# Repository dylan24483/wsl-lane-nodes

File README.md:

# wsl-lane-nodes

Phase 8 of the Westside Lanes Conqueror replacement project. Each Pi 4 controls one lane pair, replacing the QubicaAMF stack (BCU II + QBK-SIx + T-VISION + VDB-99) with direct GPIO control of the AMF 8270 cabinet I/O. Pi nodes connect to WSL-SRV via WebSocket and feed events into the existing wsl_scoring_engine.

## Status: bench rig fully validated (2026-05-06)

**What runs end-to-end on the bench:**

- [x] Pi GPIO + WebSocket + scoring engine + browser display (night-1 prototype, 2026-05-01)
- [x] AEDIKO 8-channel relay HAT + AL-ZARD DST-1R8P-P opto-input bench rig validated
- [x] Per-pair (lanes 21 + 22): 4 inputs (foul × 2 + 2nd-ball × 2) + 4 outputs (cycle × 2 + power × 2)
- [x] Both control modes proven: pulsed cycle + latched power on/off
- [x] Production safety: SIGTERM handler + `try/finally` on `pulse()` + systemd `ExecStopPost=` cleanup (3 of 4 K-mitigations; hardware watchdog is the 4th)
- [x] Foul-event vs ball-detect semantic separation (BALL_EVENT carries pin_mask + foul flag)
- [x] OpenCV pin-detect pipeline skeleton (synthetic-image self-test passes)
- [x] SQLite state persistence — server restarts don't wipe in-progress games
- [x] WebSocket protocol versioning
- [x] Server portable to WSL-SRV (Windows) or stays on Pi for dev

**Active gates before Phase 8a cutover:**

- [ ] Lane 22 characterization visit — see [docs/lane_visit_checklist.md](docs/lane_visit_checklist.md)
- [ ] T-Camera + USB capture dongle on bench — calibrate `pin_detect.PIN_SPOTS` against real frames
- [ ] Hardware watchdog perfboard build — see [docs/hardware_watchdog_design.md](docs/hardware_watchdog_design.md)

## Layout

| Path | What |
|---|---|
| `lane_node/lane_node.py` | Pi-side daemon — multi-lane GPIO, WebSocket client, signal handlers |
| `lane_node/relay_cleanup.py` | Standalone GPIO cleanup script run by systemd `ExecStopPost=` |
| `lane_node/pin_detect.py` | OpenCV pipeline skeleton + synthetic-image self-test |
| `server/lane_node_server.py` | Server — WebSocket + HTTP display + desk simulator UI + `/api/health` |
| `server/state_store.py` | SQLite persistence helpers + CLI for state inspection |
| `systemd/lane-node.service` | systemd unit for production deployment |
| `prototypes/` | Scaffolding scripts that proved individual pieces during night-1 |
| `wsl_scoring_engine.py` | Copied from wsl-systems — handles bowling logic |
| `docs/lane_visit_checklist.md` | On-site procedure for the lane characterization visit |
| `docs/hardware_watchdog_design.md` | CD4538B + MOSFET watchdog circuit spec for the 4th K-pillar |
| `docs/deploy_server_to_wsl_srv.md` | Step-by-step for moving the server to WSL-SRV |

## Run on the Pi

Two SSH sessions, server in one + lane node in the other:

```bash
# Session 1 — server
cd ~/wsl-lane-nodes && source .venv/bin/activate
WSL_MACHINE_LANES=21,22 \
WSL_SCORING_NODE_TOPOLOGY=pi-lane21-22=21,22 \
WSL_ALLOW_UNAUTHENTICATED_BENCH=1 \
python3 server/lane_node_server.py

# Session 2 — lane node daemon
cd ~/wsl-lane-nodes && source .venv/bin/activate
WSL_LANE_NODE_ID=pi-lane21-22 WSL_DIAG_SOURCE_ID=pi-lane21-22 \
WSL_LANES=21,22 WSL_ALLOW_UNAUTHENTICATED_BENCH=1 \
python3 lane_node/lane_node.py
```

Browser at `http://lane-node-dev.local:8766/` — Open Lane / Close Lane / Reset Pins / Power On/Off / Trigger Ball buttons per lane.

## Run server on WSL-SRV instead of Pi

```bash
# On WSL-SRV (Windows): see docs/deploy_server_to_wsl_srv.md
# On the Pi:
WSL_LANE_SERVER_URL=ws://192.168.4.103:8765 \
WSL_LANE_NODE_ID=pi-lane21-22 WSL_DIAG_SOURCE_ID=pi-lane21-22 \
WSL_LANES=21,22 LANE_NODE_TOKEN=<shared-secret> \
WSL_SCORING_NODE_TOKEN=<unique-pi-secret> python3 lane_node/lane_node.py
# (192.168.4.103 = WSL-SRV since the 2026-06-03 eero re-IP; confirm the live IP —
#  the DHCP reservation is still TODO. The old 192.168.86.36 is dead.)
```

## Health check

```bash
curl http://lane-node-dev.local:8766/api/health
```

Returns server uptime, connected node summary, per-lane state, pending foul flags, state DB path.

## State inspection

```bash
python3 server/state_store.py            # print current saved state
python3 server/state_store.py clear      # wipe saved state
```

## Test pin detection on synthetic frames

```bash
python3 lane_node/pin_detect.py
```

Runs 7 synthetic-image test cases (strike, gutter, head pin only down, 7-10 split, etc.) and reports pass/fail. Validates the pipeline shape; real-camera calibration of `PIN_SPOTS` is a separate step.

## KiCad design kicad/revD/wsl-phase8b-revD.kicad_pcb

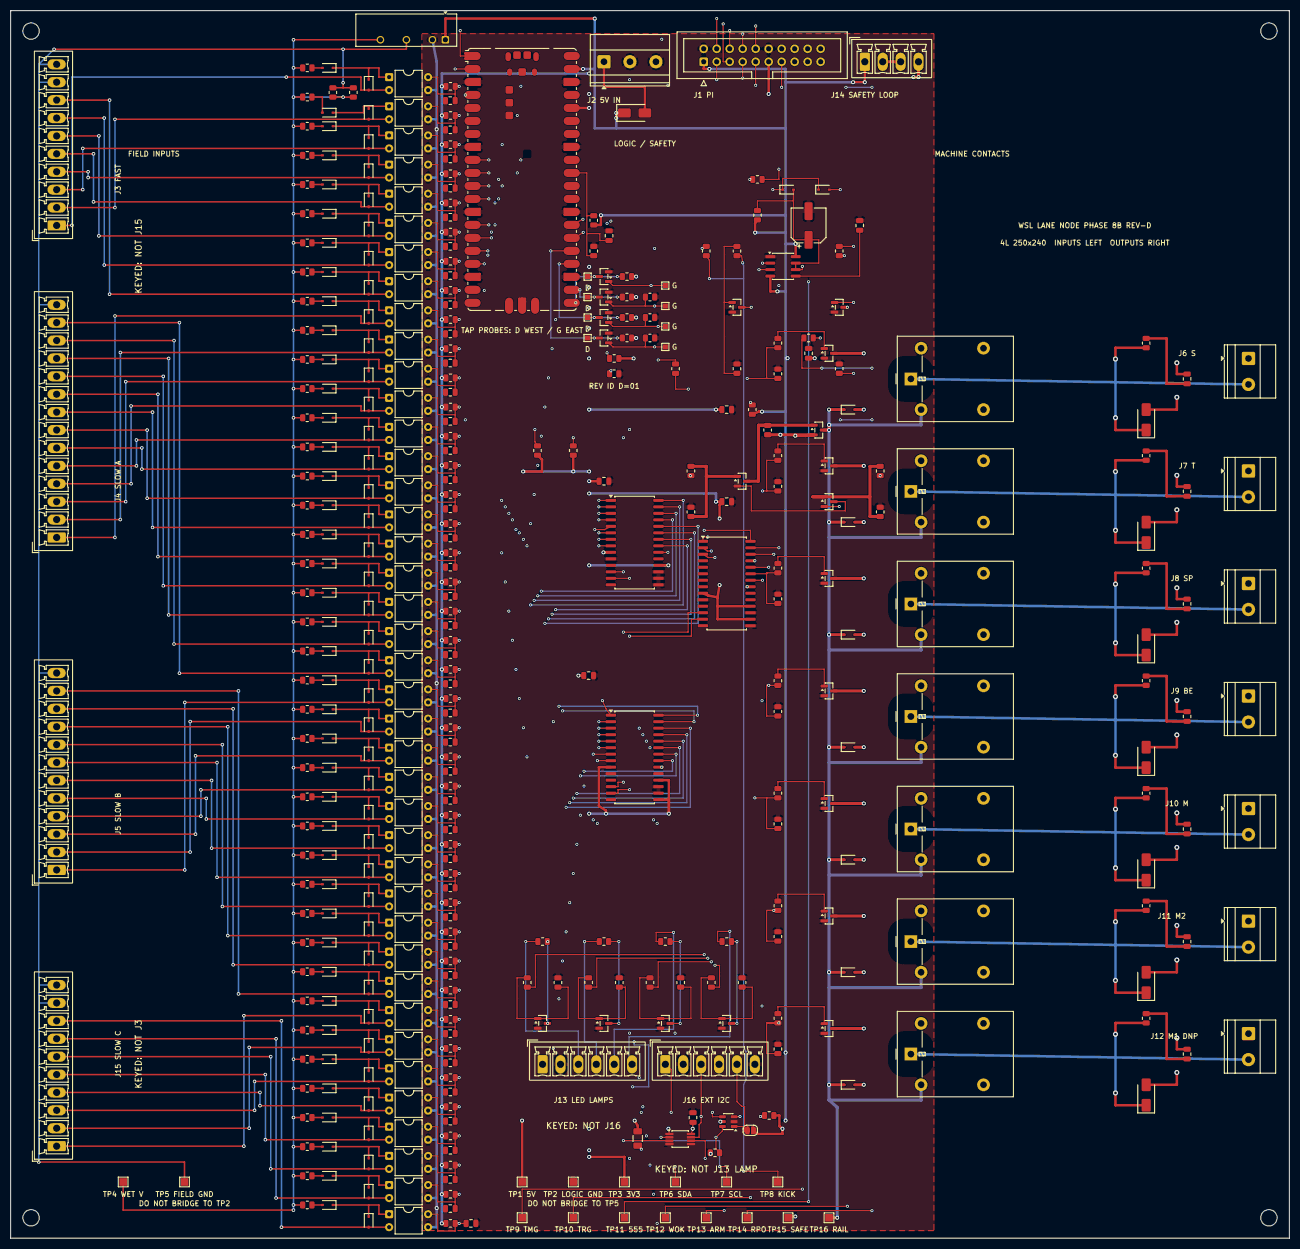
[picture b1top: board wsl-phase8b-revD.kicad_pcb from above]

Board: 4 copper layers, 250.0 x 240.0 mm, 419 parts (0 on the bottom side), 263 nets.

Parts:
A1: RP2040 Pico; RaspberryPi_Pico_SMD
C1, C2, C3, C12, C16: 0.1uF; C_0805_2012Metric
C4, C5, C6, C7, C8, C9, C10: 10nF X2 DNP; C_0805_2012Metric
C11: 100uF/16V; CP_Elec_6.3x5.4
C13: 10nF; C_0805_2012Metric
C14: 10uF; C_0805_2012Metric
C15: 100nF; C_0805_2012Metric
C17, C18, C19, C20, C21, C22, C23, C24: 10nF X7R DNP; C_0805_2012Metric
C25, C26, C27, C28, C29, C30, C31, C32, C33, C34, C35, C36, C37, C38, C39, C40, C41, C42, C43, C44, C45, C46, C47, C48, C49, C50, C51, C52, C53, C54, C55, C56: 2.2uF X7R DNP; C_0805_2012Metric
D1, D3, D5, D7, D9, D11, D13, D15, D16, D18, D19, D20, D21, D22, D23, D24, D25, D26, D27, D28, D29, D30, D31, D32, D33, D34, D35, D36, D37, D38, D39, D40, D41, D42, D43, D44, D45, D46, D47, D48, D49, D50, D51, D52, D53, D54, D55, D56, D57, D58, D59, D60, D61, D62, D63, D64, D65, D66, D67, D68, D69, D70, D71, D72, D73, D74, D75, D76, D77, D78, D79, D80, D81, D82, D83, D84, D85, D86, D87, D88, D89, D90, D91, D92, D93, D94, D95, D96, D97: 1N4148; D_SOD-323
D2, D4, D6, D8, D10, D12, D14: MOV DNP; D_SMA
D17: SS34; D_SMA
F1: 1206L020YR 200mA; Fuse_1206_3216Metric
J1: J_PI; IDC-Header_2x10_P2.54mm_Vertical
J2: J_PWR 5V; TerminalBlock_Phoenix_MKDS-1,5-3-5.08_1x03_P5.08mm_Horizont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
J3: J_FAST_IN; PhoenixContact_MCV_1,5_10-G-3.5_1x10_P3.50mm_Vertical_D1.4
J4: J_SLOW_IN_A; PhoenixContact_MCV_1,5_14-G-3.5_1x14_P3.50mm_Vertical_D1.4
J5: J_SLOW_IN_B; PhoenixContact_MCV_1,5_12-G-3.5_1x12_P3.50mm_Vertical_D1.4
J6: J_MOTION_S 5.08mm; TerminalBlock_Phoenix_MKDS-1,5-2-5.08_1x02_P5.08mm_Horizont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
J7: J_MOTION_T 5.08mm; TerminalBlock_Phoenix_MKDS-1,5-2-5.08_1x02_P5.08mm_Horizont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
J8: J_MOTION_SP 5.08mm; TerminalBlock_Phoenix_MKDS-1,5-2-5.08_1x02_P5.08mm_Horizont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
J9: J_MOTION_BE 5.08mm; TerminalBlock_Phoenix_MKDS-1,5-2-5.08_1x02_P5.08mm_Horizont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
J10: J_MOTION_M 5.08mm; TerminalBlock_Phoenix_MKDS-1,5-2-5.08_1x02_P5.08mm_Horizont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
J11: J_MOTION_M2 5.08mm; TerminalBlock_Phoenix_MKDS-1,5-2-5.08_1x02_P5.08mm_Horizont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
J12: J_MOTION_M1 5.08mm; TerminalBlock_Phoenix_MKDS-1,5-2-5.08_1x02_P5.08mm_Horizont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
J13: J_LAMP_LED; PhoenixContact_MCV_1,5_6-G-3.5_1x06_P3.50mm_Vertical_D1.4
J14: J_SAFETY; PhoenixContact_MCV_1,5_4-G-3.5_1x04_P3.50mm_Vertical_D1.4
J15: J_SLOW_IN_C; PhoenixContact_MCV_1,5_10-G-3.5_1x10_P3.50mm_Vertical_D1.4
J16: J_EXT_I2C; PhoenixContact_MCV_1,5_6-G-3.5_1x06_P3.50mm_Vertical_D1.4
JP1: 3V3 LINK OPEN DNP; SolderJumper-2_P1.3mm_Open_RoundedPad1.0x1.5mm
K1: G5LE S; Relay_SPDT_Omron-G5LE-1
K2: G5LE T; Relay_SPDT_Omron-G5LE-1
K3: G5LE SP; Relay_SPDT_Omron-G5LE-1
K4: G5LE BE; Relay_SPDT_Omron-G5LE-1
K5: G5LE M; Relay_SPDT_Omron-G5LE-1
K6: G5LE M2; Relay_SPDT_Omron-G5LE-1
K7: G5LE M1 DNP; Relay_SPDT_Omron-G5LE-1
MK1, MK2, MK3, MK4: M3; MountingHole_3.2mm_M3
Q1: MMBT3904 S; SOT-23
Q2: MMBT3904 T; SOT-23
Q3: MMBT3904 SP; SOT-23
Q4: MMBT3904 BE; SOT-23
Q5: MMBT3904 M; SOT-23
Q6: MMBT3904 M2; SOT-23
Q7: MMBT3904 M1; SOT-23
Q8: 2N7002 LED L_FIRST; SOT-23
Q9: 2N7002 LED L_SECOND; SOT-23
Q10: 2N7002 LED L_STRIKE; SOT-23
Q11: 2N7002 LED L_FOUL; SOT-23
Q12: AO3400A kick; SOT-23
Q13: AO3400A wdog; SOT-23
Q14: AO3401A rail pass; SOT-23
Q15: MMBT3904 AND ARM; SOT-23
Q16: MMBT3904 AND RP_OK; SOT-23
Q17: 2N7002LT1G TAP 555; SOT-23
Q18: 2N7002LT1G TAP KICK; SOT-23
Q19: 2N7002LT1G TAP ARM; SOT-23
Q20: 2N7002LT1G TAP RPOK; SOT-23
R1, R2, R142, R143: 4.7k; R_0805_2012Metric
R3, R5, R7, R9, R11, R13, R15, R17, R19, R21, R23, R25, R27, R29, R31, R33, R35, R37, R39, R41, R43, R45, R47, R49, R51, R53, R55, R57, R59, R61, R63, R65, R67, R69, R71, R73, R75, R77, R79, R81, R122, R123: 2k2; R_0805_2012Metric
R4, R6, R8, R10, R12, R14, R16, R18, R20, R22, R24, R26, R28, R30, R32, R34, R36, R38, R40, R42, R44, R46, R48, R50, R52, R54, R56, R58, R60, R62, R64, R66, R68, R70, R72, R74, R76, R78, R80, R82: 47k; R_0805_2012Metric
R83, R86, R89, R92, R95, R98, R101, R104, R107, R110, R113, R118, R120: 1k; R_0805_2012Metric
R84, R87, R90, R93, R96, R99, R102, R105, R108, R111, R114, R116, R124, R126, R128: 100k; R_0805_2012Metric
R85, R88, R91, R94, R97, R100, R103: 100R DNP; R_0805_2012Metric
R106, R109, R112, R115: 330R; R_0805_2012Metric
R117, R119, R121, R125, R127, R129, R130, R132, R134, R137, R140, R144, R145: 10k; R_0805_2012Metric
R131, R133, R136, R139: 1M; R_0805_2012Metric
R135, R138, R141: 10M; R_0805_2012Metric
TP1: VCC_5V; TestPoint_Pad_1.5x1.5mm
TP2: GND; TestPoint_Pad_1.5x1.5mm
TP3: VCC_3V3; TestPoint_Pad_1.5x1.5mm
TP4: FIELD_WET_V; TestPoint_Pad_1.5x1.5mm
TP5: FIELD_GND; TestPoint_Pad_1.5x1.5mm
TP6: I2C_SDA; TestPoint_Pad_1.5x1.5mm
TP7: I2C_SCL; TestPoint_Pad_1.5x1.5mm
TP8: WDOG_KICK; TestPoint_Pad_1.5x1.5mm
TP9: WDOG_TIMING_NODE; TestPoint_Pad_1.5x1.5mm
TP10: NE555_TRIG; TestPoint_Pad_1.5x1.5mm
TP11: NE555_OUT; TestPoint_Pad_1.5x1.5mm
TP12: WDOG_OK_PULLDOWN; TestPoint_Pad_1.5x1.5mm
TP13: ARM_PERMIT; TestPoint_Pad_1.5x1.5mm
TP14: RP2040_OK; TestPoint_Pad_1.5x1.5mm
TP15: SAFE_STOP_RETURN; TestPoint_Pad_1.5x1.5mm
TP16: RELAY_ENABLE_RAIL; TestPoint_Pad_1.5x1.5mm
TP17: TAP_GATE_555; TestPoint_Pad_1.0x1.0mm
TP18: TAP_NE555_OUT; TestPoint_Pad_1.0x1.0mm
TP19: TAP_GATE_KICK; TestPoint_Pad_1.0x1.0mm
TP20: TAP_WDOG_KICK; TestPoint_Pad_1.0x1.0mm
TP21: TAP_GATE_ARM; TestPoint_Pad_1.0x1.0mm
TP22: TAP_ARM_PERMIT; TestPoint_Pad_1.0x1.0mm
TP23: TAP_GATE_RPOK; TestPoint_Pad_1.0x1.0mm
TP24: TAP_RP2040_OK; TestPoint_Pad_1.0x1.0mm
U1: MCP23017 MCP_IN_A; SOIC-28W_7.5x17.9mm_P1.27mm
U2: MCP23017 MCP_IN_B; SOIC-28W_7.5x17.9mm_P1.27mm
U3: MCP23017 MCP_OUT_A; SOIC-28W_7.5x17.9mm_P1.27mm
U4: PC817 SA; DIP-4_W7.62mm
U5: PC817 SB; DIP-4_W7.62mm
U6: PC817 SC; DIP-4_W7.62mm
U7: PC817 TA1; DIP-4_W7.62mm
U8: PC817 TA2; DIP-4_W7.62mm
U9: PC817 TB; DIP-4_W7.62mm
U10: PC817 DIELL_L; DIP-4_W7.62mm
U11: PC817 DIELL_R; DIP-4_W7.62mm
U12: PC817 GS1; DIP-4_W7.62mm
U13: PC817 GS2; DIP-4_W7.62mm
U14: PC817 GS3; DIP-4_W7.62mm
U15: PC817 GS4; DIP-4_W7.62mm
U16: PC817 GS5; DIP-4_W7.62mm
U17: PC817 GS6; DIP-4_W7.62mm
U18: PC817 GS7; DIP-4_W7.62mm
U19: PC817 GS8; DIP-4_W7.62mm
U20: PC817 GS9; DIP-4_W7.62mm
U21: PC817 GS10; DIP-4_W7.62mm
U22: PC817 GP; DIP-4_W7.62mm
U23: PC817 OS; DIP-4_W7.62mm
U24: PC817 BS; DIP-4_W7.62mm
U25: PC817 PBZ; DIP-4_W7.62mm
U26: PC817 PBC; DIP-4_W7.62mm
U27: PC817 FOUL; DIP-4_W7.62mm
U28: PC817 TENTH; DIP-4_W7.62mm
U29: PC817 MAN_T; DIP-4_W7.62mm
U30: PC817 MAN_S; DIP-4_W7.62mm
U31: PC817 MAN_SWS; DIP-4_W7.62mm
U32: PC817 MAN_SWSR; DIP-4_W7.62mm
U33: PC817 AUX1; DIP-4_W7.62mm
U34: PC817 AUX2; DIP-4_W7.62mm
U35: PC817 AUX3; DIP-4_W7.62mm
U36: PC817 AUX4; DIP-4_W7.62mm
U37: PC817 AUX5; DIP-4_W7.62mm
U38: PC817 AUX6; DIP-4_W7.62mm
U39: PC817 AUX7; DIP-4_W7.62mm
U40: PC817 AUX8; DIP-4_W7.62mm
U41: PC817 AUX9; DIP-4_W7.62mm
U42: PC817 AUX10; DIP-4_W7.62mm
U43: PC817 AUX11; DIP-4_W7.62mm
U44: NE555; SOIC-8_3.9x4.9mm_P1.27mm
U45: TMA-0505S; Converter_DCDC_TRACO_TMA-05xxS_12xxS_Single_THT
U46: TCA4307DGKR; VSSOP-8_3x3mm_P0.65mm
U47: SRV05-4; SOT-23-6

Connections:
ADC_VCC5_SENSE: A1.31, C15.1, R129.2, R130.1
AND_MID_ARM_RP: Q15.2, Q16.3
ARM_PERMIT: J1.8, R125.1, R136.1, TP13.1
BASE_AND_ARM: Q15.1, R125.2, R126.1
BASE_AND_RP_OK: Q16.1, R127.2, R128.1
BASE_BE: Q4.1, R92.2
BASE_M: Q5.1, R95.2
BASE_M1: Q7.1, R101.2
BASE_M2: Q6.1, R98.2
BASE_S: Q1.1, R83.2
BASE_SP: Q3.1, R89.2
BASE_T: Q2.1, R86.2
COIL_LO_BE: D7.2, K4.5, Q4.3
COIL_LO_M: D9.2, K5.5, Q5.3
COIL_LO_M1: D13.2, K7.5, Q7.3
COIL_LO_M2: D11.2, K6.5, Q6.3
COIL_LO_S: D1.2, K1.5, Q1.3
COIL_LO_SP: D5.2, K3.5, Q3.3
COIL_LO_T: D3.2, K2.5, Q2.3
DRV_BE: R92.1, R93.1, U3.24
DRV_L_FIRST: R104.1, U3.28
DRV_L_FOUL: R113.1, U3.3
DRV_L_SECOND: R107.1, U3.1
DRV_L_STRIKE: R110.1, U3.2
DRV_M: R95.1, R96.1, U3.25
DRV_M1: R101.1, R102.1, U3.27
DRV_M2: R98.1, R99.1, U3.26
DRV_S: R83.1, R84.1, U3.21
DRV_SP: R89.1, R90.1, U3.23
DRV_T: R86.1, R87.1, U3.22
FAST_DIELL_L: A1.16, C23.1, R16.2, U10.4
FAST_DIELL_R: A1.17, C24.1, R18.2, U11.4
FAST_SA: A1.9, C17.1, R4.2, U4.4
FAST_SB: A1.10, C18.1, R6.2, U5.4
FAST_SC: A1.11, C19.1, R8.2, U6.4
FAST_TA1: A1.12, C20.1, R10.2, U7.4
FAST_TA2: A1.14, C21.1, R12.2, U8.4
FAST_TB: A1.15, C22.1, R14.2, U9.4
FIELD_FAST_DIELL_L: D31.2, J3.7, U10.2
FIELD_FAST_DIELL_R: D33.2, J3.8, U11.2
FIELD_FAST_SA: D19.2, J3.1, U4.2
FIELD_FAST_SB: D21.2, J3.2, U5.2
FIELD_FAST_SC: D23.2, J3.3, U6.2
FIELD_FAST_TA1: D25.2, J3.4, U7.2
FIELD_FAST_TA2: D27.2, J3.5, U8.2
FIELD_FAST_TB: D29.2, J3.6, U9.2
FIELD_GND: J3.9, J3.10, J4.14, J5.12, J15.9, J15.10, R122.2, R123.2, TP5.1, U45.4
FIELD_LED_AUX1: D76.1, D77.1, U33.1
FIELD_LED_AUX2: D78.1, D79.1, U34.1
FIELD_LED_AUX3: D80.1, D81.1, U35.1
FIELD_LED_AUX4: D82.1, D83.1, U36.1
FIELD_LED_AUX5: D84.1, D85.1, U37.1
FIELD_LED_AUX6: D86.1, D87.1, U38.1
FIELD_LED_AUX7: D88.1, D89.1, U39.1
FIELD_LED_AUX8: D90.1, D91.1, U40.1
FIELD_LED_AUX9: D92.1, D93.1, U41.1
FIELD_LED_AUX10: D94.1, D95.1, U42.1
FIELD_LED_AUX11: D96.1, D97.1, U43.1
FIELD_LED_BS: D58.1, D59.1, U24.1
FIELD_LED_DIELL_L: D30.1, D31.1, U10.1
FIELD_LED_DIELL_R: D32.1, D33.1, U11.1
FIELD_LED_FOUL: D64.1, D65.1, U27.1
FIELD_LED_GP: D54.1, D55.1, U22.1
FIELD_LED_GS1: D34.1, D35.1, U12.1
FIELD_LED_GS2: D36.1, D37.1, U13.1
FIELD_LED_GS3: D38.1, D39.1, U14.1
FIELD_LED_GS4: D40.1, D41.1, U15.1
FIELD_LED_GS5: D42.1, D43.1, U16.1
FIELD_LED_GS6: D44.1, D45.1, U17.1
FIELD_LED_GS7: D46.1, D47.1, U18.1
FIELD_LED_GS8: D48.1, D49.1, U19.1
FIELD_LED_GS9: D50.1, D51.1, U20.1
FIELD_LED_GS10: D52.1, D53.1, U21.1
FIELD_LED_MAN_S: D70.1, D71.1, U30.1
FIELD_LED_MAN_SWS: D72.1, D73.1, U31.1
FIELD_LED_MAN_SWSR: D74.1, D75.1, U32.1
FIELD_LED_MAN_T: D68.1, D69.1, U29.1
FIELD_LED_OS: D56.1, D57.1, U23.1
FIELD_LED_PBC: D62.1, D63.1, U26.1
FIELD_LED_PBZ: D60.1, D61.1, U25.1
FIELD_LED_SA: D18.1, D19.1, U4.1
FIELD_LED_SB: D20.1, D21.1, U5.1
FIELD_LED_SC: D22.1, D23.1, U6.1
FIELD_LED_TA1: D24.1, D25.1, U7.1
FIELD_LED_TA2: D26.1, D27.1, U8.1
FIELD_LED_TB: D28.1, D29.1, U9.1
FIELD_LED_TENTH: D66.1, D67.1, U28.1
FIELD_RIN_AUX1: D76.2, R61.2
FIELD_RIN_AUX2: D78.2, R63.2
FIELD_RIN_AUX3: D80.2, R65.2
FIELD_RIN_AUX4: D82.2, R67.2
FIELD_RIN_AUX5: D84.2, R69.2
FIELD_RIN_AUX6: D86.2, R71.2
FIELD_RIN_AUX7: D88.2, R73.2
FIELD_RIN_AUX8: D90.2, R75.2
FIELD_RIN_AUX9: D92.2, R77.2
FIELD_RIN_AUX10: D94.2, R79.2
FIELD_RIN_AUX11: D96.2, R81.2
FIELD_RIN_BS: D58.2, R43.2
FIELD_RIN_DIELL_L: D30.2, R15.2
FIELD_RIN_DIELL_R: D32.2, R17.2
FIELD_RIN_FOUL: D64.2, R49.2
FIELD_RIN_GP: D54.2, R39.2
FIELD_RIN_GS1: D34.2, R19.2
FIELD_RIN_GS2: D36.2, R21.2
FIELD_RIN_GS3: D38.2, R23.2
FIELD_RIN_GS4: D40.2, R25.2
FIELD_RIN_GS5: D42.2, R27.2
FIELD_RIN_GS6: D44.2, R29.2
FIELD_RIN_GS7: D46.2, R31.2
FIELD_RIN_GS8: D48.2, R33.2
FIELD_RIN_GS9: D50.2, R35.2
FIELD_RIN_GS10: D52.2, R37.2
FIELD_RIN_MAN_S: D70.2, R55.2
FIELD_RIN_MAN_SWS: D72.2, R57.2
FIELD_RIN_MAN_SWSR: D74.2, R59.2
FIELD_RIN_MAN_T: D68.2, R53.2
FIELD_RIN_OS: D56.2, R41.2
FIELD_RIN_PBC: D62.2, R47.2
FIELD_RIN_PBZ: D60.2, R45.2
FIELD_RIN_SA: D18.2, R3.2
FIELD_RIN_SB: D20.2, R5.2
FIELD_RIN_SC: D22.2, R7.2
FIELD_RIN_TA1: D24.2, R9.2
FIELD_RIN_TA2: D26.2, R11.2
FIELD_RIN_TB: D28.2, R13.2
FIELD_RIN_TENTH: D66.2, R51.2
FIELD_SLOW_AUX1: D77.2, J5.9, U33.2
FIELD_SLOW_AUX2: D79.2, J5.10, U34.2
FIELD_SLOW_AUX3: D81.2, J5.11, U35.2
FIELD_SLOW_AUX4: D83.2, J15.1, U36.2
FIELD_SLOW_AUX5: D85.2, J15.2, U37.2
FIELD_SLOW_AUX6: D87.2, J15.3, U38.2
FIELD_SLOW_AUX7: D89.2, J15.4, U39.2
FIELD_SLOW_AUX8: D91.2, J15.5, U40.2
FIELD_SLOW_AUX9: D93.2, J15.6, U41.2
FIELD_SLOW_AUX10: D95.2, J15.7, U42.2
FIELD_SLOW_AUX11: D97.2, J15.8, U43.2
FIELD_SLOW_BS: D59.2, J4.13, U24.2
FIELD_SLOW_FOUL: D65.2, J5.3, U27.2
FIELD_SLOW_GP: D55.2, J4.11, U22.2
FIELD_SLOW_GS1: D35.2, J4.1, U12.2
FIELD_SLOW_GS2: D37.2, J4.2, U13.2
FIELD_SLOW_GS3: D39.2, J4.3, U14.2
FIELD_SLOW_GS4: D41.2, J4.4, U15.2
FIELD_SLOW_GS5: D43.2, J4.5, U16.2
FIELD_SLOW_GS6: D45.2, J4.6, U17.2
FIELD_SLOW_GS7: D47.2, J4.7, U18.2
FIELD_SLOW_GS8: D49.2, J4.8, U19.2
FIELD_SLOW_GS9: D51.2, J4.9, U20.2
FIELD_SLOW_GS10: D53.2, J4.10, U21.2
FIELD_SLOW_MAN_S: D71.2, J5.6, U30.2
FIELD_SLOW_MAN_SWS: D73.2, J5.7, U31.2
FIELD_SLOW_MAN_SWSR: D75.2, J5.8, U32.2
FIELD_SLOW_MAN_T: D69.2, J5.5, U29.2
FIELD_SLOW_OS: D57.2, J4.12, U23.2
FIELD_SLOW_PBC: D63.2, J5.2, U26.2
FIELD_SLOW_PBZ: D61.2, J5.1, U25.2
FIELD_SLOW_TENTH: D67.2, J5.4, U28.2
FIELD_WET_V: R3.1, R5.1, R7.1, R9.1, R11.1, R13.1, R15.1, R17.1, R19.1, R21.1, R23.1, R25.1, R27.1, R29.1, R31.1, R33.1, R35.1, R37.1, R39.1, R41.1, R43.1, R45.1, R47.1, R49.1, R51.1, R53.1, R55.1, R57.1, R59.1, R61.1, R63.1, R65.1, R67.1, R69.1, R71.1, R73.1, R75.1, R77.1, R79.1, R81.1, R122.1, R123.1, TP4.1, U45.6
GND: A1.3, A1.8, A1.13, A1.18, A1.23, A1.28, A1.33, A1.38, C1.2, C2.2, C3.2, C11.2, C12.2, C13.2, C14.2, C15.2, C16.2, C17.2, C18.2, C19.2, C20.2, C21.2, C22.2, C23.2, C24.2, C25.2, C26.2, C27.2, C28.2, C29.2, C30.2, C31.2, C32.2, C33.2, C34.2, C35.2, C36.2, C37.2, C38.2, C39.2, C40.2, C41.2, C42.2, C43.2, C44.2, C45.2, C46.2, C47.2, C48.2, C49.2, C50.2, C51.2, C52.2, C53.2, C54.2, C55.2, C56.2, J1.2, J1.12, J2.2, J2.3, J13.2, J16.2, J16.6, Q1.2, Q2.2, Q3.2, Q4.2, Q5.2, Q6.2, Q7.2, Q8.2, Q9.2, Q10.2, Q11.2, Q12.2, Q13.2, Q17.2, Q18.2, Q19.2, Q20.2, R84.2, R87.2, R90.2, R93.2, R96.2, R99.2, R102.2, R105.2, R108.2, R111.2, R114.2, R119.2, R121.2, R126.2, R128.2, R130.2, R135.2, R138.2, R141.2, R145.1, TP2.1, U1.10, U1.15, U1.16, U1.17, U2.10, U2.16, U2.17, U3.10, U3.15, U3.17, U4.3, U5.3, U6.3, U7.3, U8.3, U9.3, U10.3, U11.3, U12.3, U13.3, U14.3, U15.3, U16.3, U17.3, U18.3, U19.3, U20.3, U21.3, U22.3, U23.3, U24.3, U25.3, U26.3, U27.3, U28.3, U29.3, U30.3, U31.3, U32.3, U33.3, U34.3, U35.3, U36.3, U37.3, U38.3, U39.3, U40.3, U41.3, U42.3, U43.3, U44.1, U45.2, U46.4, U47.2
I2C_SCL: J1.4, R2.2, TP7.1, U1.12, U2.12, U3.12, U46.3
I2C_SDA: J1.3, R1.2, TP6.1, U1.13, U2.13, U3.13, U46.6
J16_3V3: J16.5, JP1.2, U47.1
J16_5V: F1.2, J16.1, U47.4
J16_SCL: J16.4, R143.2, U46.2, U47.6
J16_SDA: J16.3, R142.2, U46.7, U47.3
LED_GATE_L_FIRST: Q8.1, R104.2, R105.1
LED_GATE_L_FOUL: Q11.1, R113.2, R114.1
LED_GATE_L_SECOND: Q9.1, R107.2, R108.1
LED_GATE_L_STRIKE: Q10.1, R110.2, R111.1
LED_L_FIRST_RETURN: J13.3, R106.1
LED_L_FOUL_RETURN: J13.6, R115.1
LED_L_SECOND_RETURN: J13.4, R109.1
LED_L_STRIKE_RETURN: J13.5, R112.1
LED_SINK_L_FIRST: Q8.3, R106.2
LED_SINK_L_FOUL: Q11.3, R115.2
LED_SINK_L_SECOND: Q9.3, R109.2
LED_SINK_L_STRIKE: Q10.3, R112.2
MCP_INT_A: J1.9, U1.20
MCP_INT_B: J1.10, U2.20
NE555_CTRL: C13.1, U44.5
NE555_OUT: R120.1, R131.1, TP11.1, U44.3
NE555_TRIG: D16.2, R117.2, TP10.1, U44.2
OUT_BE_A: D8.1, J9.2, K4.1, R94.1
OUT_BE_B: C7.2, D8.2, J9.1, K4.3
OUT_M1_A: D14.1, J12.2, K7.1, R103.1
OUT_M1_B: C10.2, D14.2, J12.1, K7.3
OUT_M2_A: D12.1, J11.2, K6.1, R100.1
OUT_M2_B: C9.2, D12.2, J11.1, K6.3
OUT_M_A: D10.1, J10.2, K5.1, R97.1
OUT_M_B: C8.2, D10.2, J10.1, K5.3
OUT_SP_A: D6.1, J8.2, K3.1, R91.1
OUT_SP_B: C6.2, D6.2, J8.1, K3.3
OUT_S_A: D2.1, J6.2, K1.1, R85.1
OUT_S_B: C4.2, D2.2, J6.1, K1.3
OUT_T_A: D4.1, J7.2, K2.1, R88.1
OUT_T_B: C5.2, D4.2, J7.1, K2.3
PI_UART_RX: A1.1, J1.6
PI_UART_TX: A1.2, J1.5
RAIL_GATE: Q14.1, Q15.3, R124.2
RELAY_ENABLE_RAIL: D1.1, D3.1, D5.1, D7.1, D9.1, D11.1, D13.1, K1.2, K2.2, K3.2, K4.2, K5.2, K6.2, K7.2, Q14.3, TP16.1
REV_ID0: A1.26, R144.2
REV_ID1: A1.27, R145.2
RP2040_OK: A1.4, J1.13, R127.1, R139.1, TP14.1
SAFE_STOP_RETURN: J14.4, Q14.2, R124.1, TP15.1
SAFE_TBSC_RETURN: J14.2, J14.3
SLOW_AUX1: C46.1, R62.2, U2.26, U33.4
SLOW_AUX2: C47.1, R64.2, U2.27, U34.4
SLOW_AUX3: C48.1, R66.2, U2.28, U35.4
SLOW_AUX4: C49.1, R68.2, U2.1, U36.4
SLOW_AUX5: C50.1, R70.2, U2.2, U37.4
SLOW_AUX6: C51.1, R72.2, U2.3, U38.4
SLOW_AUX7: C52.1, R74.2, U2.4, U39.4
SLOW_AUX8: C53.1, R76.2, U2.5, U40.4
SLOW_AUX9: C54.1, R78.2, U2.6, U41.4
SLOW_AUX10: C55.1, R80.2, U2.7, U42.4
SLOW_AUX11: C56.1, R82.2, U2.8, U43.4
SLOW_BS: C37.1, R44.2, U1.5, U24.4
SLOW_FOUL: C40.1, R50.2, U1.8, U27.4
SLOW_GP: C35.1, R40.2, U1.3, U22.4
SLOW_GS1: C25.1, R20.2, U1.21, U12.4
SLOW_GS2: C26.1, R22.2, U1.22, U13.4
SLOW_GS3: C27.1, R24.2, U1.23, U14.4
SLOW_GS4: C28.1, R26.2, U1.24, U15.4
SLOW_GS5: C29.1, R28.2, U1.25, U16.4
SLOW_GS6: C30.1, R30.2, U1.26, U17.4
SLOW_GS7: C31.1, R32.2, U1.27, U18.4
SLOW_GS8: C32.1, R34.2, U1.28, U19.4
SLOW_GS9: C33.1, R36.2, U1.1, U20.4
SLOW_GS10: C34.1, R38.2, U1.2, U21.4
SLOW_MAN_S: C43.1, R56.2, U2.23, U30.4
SLOW_MAN_SWS: C44.1, R58.2, U2.24, U31.4
SLOW_MAN_SWSR: C45.1, R60.2, U2.25, U32.4
SLOW_MAN_T: C42.1, R54.2, U2.22, U29.4
SLOW_OS: C36.1, R42.2, U1.4, U23.4
SLOW_PBC: C39.1, R48.2, U1.7, U26.4
SLOW_PBZ: C38.1, R46.2, U1.6, U25.4
SLOW_TENTH: C41.1, R52.2, U2.21, U28.4
SNUB_BE: C7.1, R94.2
SNUB_M: C8.1, R97.2
SNUB_M1: C10.1, R103.2
SNUB_M2: C9.1, R100.2
SNUB_S: C4.1, R85.2
SNUB_SP: C6.1, R91.2
SNUB_T: C5.1, R88.2
TAP_ARM_PERMIT: A1.24, Q19.3, R137.2, TP22.1
TAP_GATE_555: Q17.1, R131.2, TP17.1
TAP_GATE_ARM: Q19.1, R136.2, R138.1, TP21.1
TAP_GATE_KICK: Q18.1, R133.2, R135.1, TP19.1
TAP_GATE_RPOK: Q20.1, R139.2, R141.1, TP23.1
TAP_NE555_OUT: A1.21, Q17.3, R132.2, TP18.1
TAP_RP2040_OK: A1.25, Q20.3, R140.2, TP24.1
TAP_WDOG_KICK: A1.22, Q18.3, R134.2, TP20.1
VCC_3V3: A1.36, C1.1, C2.1, C3.1, C14.1, C16.1, J1.11, JP1.1, R1.1, R2.1, R4.1, R6.1, R8.1, R10.1, R12.1, R14.1, R16.1, R18.1, R20.1, R22.1, R24.1, R26.1, R28.1, R30.1, R32.1, R34.1, R36.1, R38.1, R40.1, R42.1, R44.1, R46.1, R48.1, R50.1, R52.1, R54.1, R56.1, R58.1, R60.1, R62.1, R64.1, R66.1, R68.1, R70.1, R72.1, R74.1, R76.1, R78.1, R80.1, R82.1, R132.1, R134.1, R137.1, R140.1, R142.1, R143.1, R144.1, TP3.1, U1.9, U1.18, U2.9, U2.15, U2.18, U3.9, U3.16, U3.18, U46.1, U46.8
VCC_5V: A1.39, C12.1, D17.1, F1.1, J1.1, J13.1, J14.1, R116.1, R117.1, R129.1, TP1.1, U44.4, U44.8, U45.1, U47.5
VCC_5V_RAW: D17.2, J2.1
WDOG_KICK: J1.7, R118.1, R133.1, TP8.1
WDOG_KICK_DRAIN: D15.1, D16.1, Q12.3
WDOG_KICK_GATE: Q12.1, R118.2, R119.1
WDOG_OK_GATE: Q13.1, R120.2, R121.1
WDOG_OK_PULLDOWN: Q13.3, Q16.2, TP12.1
WDOG_TIMING_NODE: C11.1, D15.2, R116.2, TP9.1, U44.6, U44.7

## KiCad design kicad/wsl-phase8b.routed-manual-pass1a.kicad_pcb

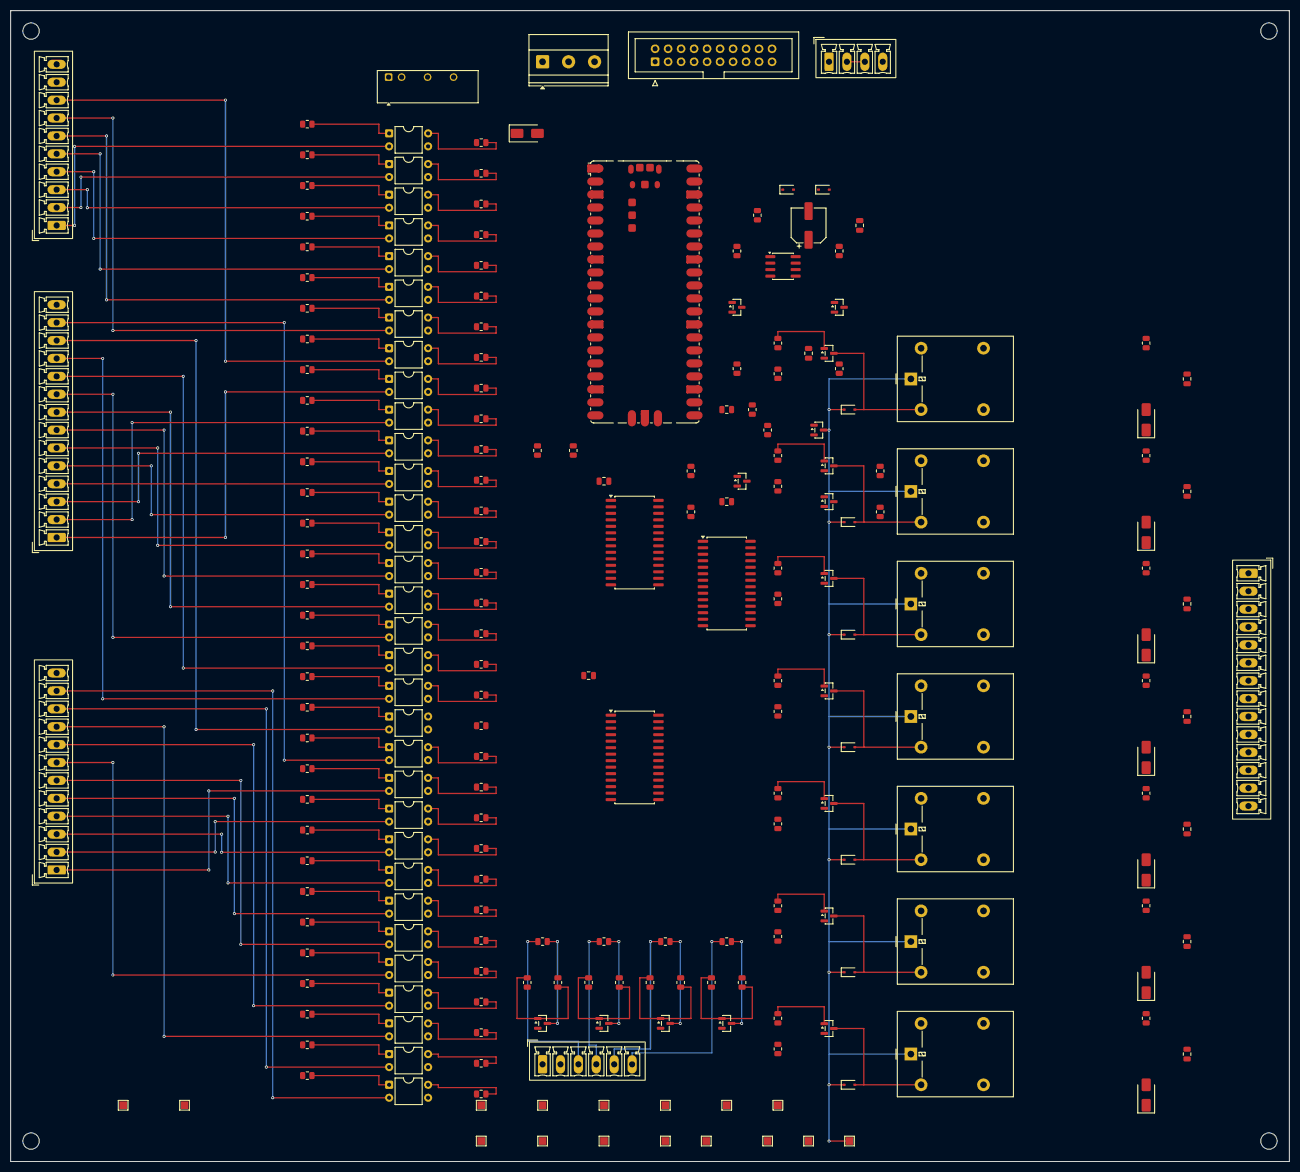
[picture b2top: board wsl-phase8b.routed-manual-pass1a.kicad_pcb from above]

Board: 4 copper layers, 250.0 x 225.0 mm, 230 parts (0 on the bottom side), 184 nets.

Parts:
A1: RP2040 Pico; RaspberryPi_Pico_SMD
C1, C2, C3, C12: 0.1uF; C_0805_2012Metric
C4, C5, C6, C7, C8, C9, C10: 10nF X2 DNP; C_0805_2012Metric
C11: 100uF/16V; CP_Elec_6.3x5.4
C13: 10nF; C_0805_2012Metric
C14: 10uF; C_0805_2012Metric
D1, D3, D5, D7, D9, D11, D13, D15, D16: 1N4148; D_SOD-323
D2, D4, D6, D8, D10, D12, D14: MOV DNP; D_SMA
D17: SS14; D_SMA
J1: J_PI; IDC-Header_2x10_P2.54mm_Vertical
J2: J_PWR 5V; TerminalBlock_Phoenix_MKDS-1,5-3-5.08_1x03_P5.08mm_Horizont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
J3: J_FAST_IN; PhoenixContact_MCV_1,5_10-G-3.5_1x10_P3.50mm_Vertical
J4: J_SLOW_IN_A; PhoenixContact_MCV_1,5_14-G-3.5_1x14_P3.50mm_Vertical
J5: J_SLOW_IN_B; PhoenixContact_MCV_1,5_12-G-3.5_1x12_P3.50mm_Vertical
J6: J_MOTION_OUT; PhoenixContact_MCV_1,5_14-G-3.5_1x14_P3.50mm_Vertical
J7: J_LAMP_LED; PhoenixContact_MCV_1,5_6-G-3.5_1x06_P3.50mm_Vertical
J8: J_SAFETY; PhoenixContact_MCV_1,5_4-G-3.5_1x04_P3.50mm_Vertical
K1: G5LE S; Relay_SPDT_Omron-G5LE-1
K2: G5LE T; Relay_SPDT_Omron-G5LE-1
K3: G5LE SP; Relay_SPDT_Omron-G5LE-1
K4: G5LE BE; Relay_SPDT_Omron-G5LE-1
K5: G5LE M; Relay_SPDT_Omron-G5LE-1
K6: G5LE M2; Relay_SPDT_Omron-G5LE-1
K7: G5LE M1 DNP; Relay_SPDT_Omron-G5LE-1
MK1, MK2, MK3, MK4: M3; MountingHole_3.2mm_M3
Q1: MMBT3904 S; SOT-23
Q2: MMBT3904 T; SOT-23
Q3: MMBT3904 SP; SOT-23
Q4: MMBT3904 BE; SOT-23
Q5: MMBT3904 M; SOT-23
Q6: MMBT3904 M2; SOT-23
Q7: MMBT3904 M1; SOT-23
Q8: 2N7002 LED L_FIRST; SOT-23
Q9: 2N7002 LED L_SECOND; SOT-23
Q10: 2N7002 LED L_STRIKE; SOT-23
Q11: 2N7002 LED L_FOUL; SOT-23
Q12: AO3400A kick; SOT-23
Q13: AO3400A wdog; SOT-23
Q14: AO3401A rail pass; SOT-23
Q15: AND ARM; SOT-23
Q16: AND RP_OK; SOT-23
R1, R2: 4.7k; R_0805_2012Metric
R3, R5, R7, R9, R11, R13, R15, R17, R19, R21, R23, R25, R27, R29, R31, R33, R35, R37, R39, R41, R43, R45, R47, R49, R51, R53, R55, R57, R59, R61, R63, R65: 2k2; R_0805_2012Metric
R4, R6, R8, R10, R12, R14, R16, R18, R20, R22, R24, R26, R28, R30, R32, R34, R36, R38, R40, R42, R44, R46, R48, R50, R52, R54, R56, R58, R60, R62, R64, R66, R101, R103, R105, R107, R109: 10k; R_0805_2012Metric
R67, R70, R73, R76, R79, R82, R85, R88, R91, R94, R97, R102, R104: 1k; R_0805_2012Metric
R68, R71, R74, R77, R80, R83, R86, R89, R92, R95, R98, R100, R106, R108, R110: 100k; R_0805_2012Metric
R69, R72, R75, R78, R81, R84, R87: 100R DNP; R_0805_2012Metric
R90, R93, R96, R99: 330R TBD; R_0805_2012Metric
TP1: VCC_5V; TestPoint_Pad_1.5x1.5mm
TP2: GND; TestPoint_Pad_1.5x1.5mm
TP3: VCC_3V3; TestPoint_Pad_1.5x1.5mm
TP4: FIELD_WET_V; TestPoint_Pad_1.5x1.5mm
TP5: FIELD_GND; TestPoint_Pad_1.5x1.5mm
TP6: I2C_SDA; TestPoint_Pad_1.5x1.5mm
TP7: I2C_SCL; TestPoint_Pad_1.5x1.5mm
TP8: WDOG_KICK; TestPoint_Pad_1.5x1.5mm
TP9: WDOG_TIMING_NODE; TestPoint_Pad_1.5x1.5mm
TP10: NE555_TRIG; TestPoint_Pad_1.5x1.5mm
TP11: NE555_OUT; TestPoint_Pad_1.5x1.5mm
TP12: WDOG_OK_PULLDOWN; TestPoint_Pad_1.5x1.5mm
TP13: ARM_PERMIT; TestPoint_Pad_1.5x1.5mm
TP14: RP2040_OK; TestPoint_Pad_1.5x1.5mm
TP15: SAFE_STOP_RETURN; TestPoint_Pad_1.5x1.5mm
TP16: RELAY_ENABLE_RAIL; TestPoint_Pad_1.5x1.5mm
U1: MCP23017 MCP_IN_A; SOIC-28W_7.5x17.9mm_P1.27mm
U2: MCP23017 MCP_IN_B; SOIC-28W_7.5x17.9mm_P1.27mm
U3: MCP23017 MCP_OUT_A; SOIC-28W_7.5x17.9mm_P1.27mm
U4: PC817 SA; DIP-4_W7.62mm
U5: PC817 SB; DIP-4_W7.62mm
U6: PC817 SC; DIP-4_W7.62mm
U7: PC817 TA1; DIP-4_W7.62mm
U8: PC817 TA2; DIP-4_W7.62mm
U9: PC817 TB; DIP-4_W7.62mm
U10: PC817 DIELL_L; DIP-4_W7.62mm
U11: PC817 DIELL_R; DIP-4_W7.62mm
U12: PC817 GS1; DIP-4_W7.62mm
U13: PC817 GS2; DIP-4_W7.62mm
U14: PC817 GS3; DIP-4_W7.62mm
U15: PC817 GS4; DIP-4_W7.62mm
U16: PC817 GS5; DIP-4_W7.62mm
U17: PC817 GS6; DIP-4_W7.62mm
U18: PC817 GS7; DIP-4_W7.62mm
U19: PC817 GS8; DIP-4_W7.62mm
U20: PC817 GS9; DIP-4_W7.62mm
U21: PC817 GS10; DIP-4_W7.62mm
U22: PC817 GP; DIP-4_W7.62mm
U23: PC817 OS; DIP-4_W7.62mm
U24: PC817 BS; DIP-4_W7.62mm
U25: PC817 PBZ; DIP-4_W7.62mm
U26: PC817 PBC; DIP-4_W7.62mm
U27: PC817 FOUL; DIP-4_W7.62mm
U28: PC817 TENTH; DIP-4_W7.62mm
U29: PC817 MAN_T; DIP-4_W7.62mm
U30: PC817 MAN_S; DIP-4_W7.62mm
U31: PC817 MAN_SWS; DIP-4_W7.62mm
U32: PC817 MAN_SWSR; DIP-4_W7.62mm
U33: PC817 AUX1; DIP-4_W7.62mm
U34: PC817 AUX2; DIP-4_W7.62mm
U35: PC817 AUX3; DIP-4_W7.62mm
U36: NE555; SOIC-8_3.9x4.9mm_P1.27mm
U37: TMA-0505S; Converter_DCDC_TRACO_TMA-05xxS_12xxS_Single_THT

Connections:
AND_MID_ARM_RP: Q15.2, Q16.3
ARM_PERMIT: J1.8, R107.1, TP13.1
BASE_AND_ARM: Q15.1, R107.2, R108.1
BASE_AND_RP_OK: Q16.1, R109.2, R110.1
BASE_BE: Q4.1, R76.2
BASE_M: Q5.1, R79.2
BASE_M1: Q7.1, R85.2
BASE_M2: Q6.1, R82.2
BASE_S: Q1.1, R67.2
BASE_SP: Q3.1, R73.2
BASE_T: Q2.1, R70.2
COIL_LO_BE: D7.2, K4.2, Q4.3
COIL_LO_M: D9.2, K5.2, Q5.3
COIL_LO_M1: D13.2, K7.2, Q7.3
COIL_LO_M2: D11.2, K6.2, Q6.3
COIL_LO_S: D1.2, K1.2, Q1.3
COIL_LO_SP: D5.2, K3.2, Q3.3
COIL_LO_T: D3.2, K2.2, Q2.3
DRV_BE: R76.1, R77.1, U3.24
DRV_L_FIRST: R88.1, U3.28
DRV_L_FOUL: R97.1, U3.3
DRV_L_SECOND: R91.1, U3.1
DRV_L_STRIKE: R94.1, U3.2
DRV_M: R79.1, R80.1, U3.25
DRV_M1: R85.1, R86.1, U3.27
DRV_M2: R82.1, R83.1, U3.26
DRV_S: R67.1, R68.1, U3.21
DRV_SP: R73.1, R74.1, U3.23
DRV_T: R70.1, R71.1, U3.22
FAST_DIELL_L: A1.16, R16.2, U10.4
FAST_DIELL_R: A1.17, R18.2, U11.4
FAST_SA: A1.9, R4.2, U4.4
FAST_SB: A1.10, R6.2, U5.4
FAST_SC: A1.11, R8.2, U6.4
FAST_TA1: A1.12, R10.2, U7.4
FAST_TA2: A1.14, R12.2, U8.4
FAST_TB: A1.15, R14.2, U9.4
FIELD_FAST_DIELL_L: J3.7, U10.2
FIELD_FAST_DIELL_R: J3.8, U11.2
FIELD_FAST_SA: J3.1, U4.2
FIELD_FAST_SB: J3.2, U5.2
FIELD_FAST_SC: J3.3, U6.2
FIELD_FAST_TA1: J3.4, U7.2
FIELD_FAST_TA2: J3.5, U8.2
FIELD_FAST_TB: J3.6, U9.2
FIELD_GND: J3.9, J3.10, J4.14, J5.12, TP5.1, U37.4
FIELD_LED_AUX1: R61.2, U33.1
FIELD_LED_AUX2: R63.2, U34.1
FIELD_LED_AUX3: R65.2, U35.1
FIELD_LED_BS: R43.2, U24.1
FIELD_LED_DIELL_L: R15.2, U10.1
FIELD_LED_DIELL_R: R17.2, U11.1
FIELD_LED_FOUL: R49.2, U27.1
FIELD_LED_GP: R39.2, U22.1
FIELD_LED_GS1: R19.2, U12.1
FIELD_LED_GS2: R21.2, U13.1
FIELD_LED_GS3: R23.2, U14.1
FIELD_LED_GS4: R25.2, U15.1
FIELD_LED_GS5: R27.2, U16.1
FIELD_LED_GS6: R29.2, U17.1
FIELD_LED_GS7: R31.2, U18.1
FIELD_LED_GS8: R33.2, U19.1
FIELD_LED_GS9: R35.2, U20.1
FIELD_LED_GS10: R37.2, U21.1
FIELD_LED_MAN_S: R55.2, U30.1
FIELD_LED_MAN_SWS: R57.2, U31.1
FIELD_LED_MAN_SWSR: R59.2, U32.1
FIELD_LED_MAN_T: R53.2, U29.1
FIELD_LED_OS: R41.2, U23.1
FIELD_LED_PBC: R47.2, U26.1
FIELD_LED_PBZ: R45.2, U25.1
FIELD_LED_SA: R3.2, U4.1
FIELD_LED_SB: R5.2, U5.1
FIELD_LED_SC: R7.2, U6.1
FIELD_LED_TA1: R9.2, U7.1
FIELD_LED_TA2: R11.2, U8.1
FIELD_LED_TB: R13.2, U9.1
FIELD_LED_TENTH: R51.2, U28.1
FIELD_SLOW_AUX1: J5.9, U33.2
FIELD_SLOW_AUX2: J5.10, U34.2
FIELD_SLOW_AUX3: J5.11, U35.2
FIELD_SLOW_BS: J4.13, U24.2
FIELD_SLOW_FOUL: J5.3, U27.2
FIELD_SLOW_GP: J4.11, U22.2
FIELD_SLOW_GS1: J4.1, U12.2
FIELD_SLOW_GS2: J4.2, U13.2
FIELD_SLOW_GS3: J4.3, U14.2
FIELD_SLOW_GS4: J4.4, U15.2
FIELD_SLOW_GS5: J4.5, U16.2
FIELD_SLOW_GS6: J4.6, U17.2
FIELD_SLOW_GS7: J4.7, U18.2
FIELD_SLOW_GS8: J4.8, U19.2
FIELD_SLOW_GS9: J4.9, U20.2
FIELD_SLOW_GS10: J4.10, U21.2
FIELD_SLOW_MAN_S: J5.6, U30.2
FIELD_SLOW_MAN_SWS: J5.7, U31.2
FIELD_SLOW_MAN_SWSR: J5.8, U32.2
FIELD_SLOW_MAN_T: J5.5, U29.2
FIELD_SLOW_OS: J4.12, U23.2
FIELD_SLOW_PBC: J5.2, U26.2
FIELD_SLOW_PBZ: J5.1, U25.2
FIELD_SLOW_TENTH: J5.4, U28.2
FIELD_WET_V: R3.1, R5.1, R7.1, R9.1, R11.1, R13.1, R15.1, R17.1, R19.1, R21.1, R23.1, R25.1, R27.1, R29.1, R31.1, R33.1, R35.1, R37.1, R39.1, R41.1, R43.1, R45.1, R47.1, R49.1, R51.1, R53.1, R55.1, R57.1, R59.1, R61.1, R63.1, R65.1, TP4.1, U37.6
GND: A1.3, A1.8, A1.13, A1.18, A1.23, A1.28, A1.33, A1.38, C1.2, C2.2, C3.2, C11.2, C12.2, C13.2, C14.2, J1.2, J1.12, J2.2, J2.3, J7.2, Q1.2, Q2.2, Q3.2, Q4.2, Q5.2, Q6.2, Q7.2, Q8.2, Q9.2, Q10.2, Q11.2, Q12.2, Q13.2, R68.2, R71.2, R74.2, R77.2, R80.2, R83.2, R86.2, R89.2, R92.2, R95.2, R98.2, R103.2, R105.2, R108.2, R110.2, TP2.1, U1.10, U1.15, U1.16, U1.17, U2.10, U2.16, U2.17, U3.10, U3.15, U3.17, U4.3, U5.3, U6.3, U7.3, U8.3, U9.3, U10.3, U11.3, U12.3, U13.3, U14.3, U15.3, U16.3, U17.3, U18.3, U19.3, U20.3, U21.3, U22.3, U23.3, U24.3, U25.3, U26.3, U27.3, U28.3, U29.3, U30.3, U31.3, U32.3, U33.3, U34.3, U35.3, U36.1, U37.2
I2C_SCL: J1.4, R2.2, TP7.1, U1.12, U2.12, U3.12
I2C_SDA: J1.3, R1.2, TP6.1, U1.13, U2.13, U3.13
LED_GATE_L_FIRST: Q8.1, R88.2, R89.1
LED_GATE_L_FOUL: Q11.1, R97.2, R98.1
LED_GATE_L_SECOND: Q9.1, R91.2, R92.1
LED_GATE_L_STRIKE: Q10.1, R94.2, R95.1
LED_L_FIRST_RETURN: J7.3, R90.1
LED_L_FOUL_RETURN: J7.6, R99.1
LED_L_SECOND_RETURN: J7.4, R93.1
LED_L_STRIKE_RETURN: J7.5, R96.1
LED_SINK_L_FIRST: Q8.3, R90.2
LED_SINK_L_FOUL: Q11.3, R99.2
LED_SINK_L_SECOND: Q9.3, R93.2
LED_SINK_L_STRIKE: Q10.3, R96.2
MCP_INT_A: J1.9, U1.20
MCP_INT_B: J1.10, U2.20
NE555_CTRL: C13.1, U36.5
NE555_OUT: R104.1, TP11.1, U36.3
NE555_TRIG: D16.2, R101.2, TP10.1, U36.2
OUT_BE_A: D8.1, J6.7, K4.3, R78.1
OUT_BE_B: C7.2, D8.2, J6.8, K4.4
OUT_M1_A: D14.1, J6.13, K7.3, R87.1
OUT_M1_B: C10.2, D14.2, J6.14, K7.4
OUT_M2_A: D12.1, J6.11, K6.3, R84.1
OUT_M2_B: C9.2, D12.2, J6.12, K6.4
OUT_M_A: D10.1, J6.9, K5.3, R81.1
OUT_M_B: C8.2, D10.2, J6.10, K5.4
OUT_SP_A: D6.1, J6.5, K3.3, R75.1
OUT_SP_B: C6.2, D6.2, J6.6, K3.4
OUT_S_A: D2.1, J6.1, K1.3, R69.1
OUT_S_B: C4.2, D2.2, J6.2, K1.4
OUT_T_A: D4.1, J6.3, K2.3, R72.1
OUT_T_B: C5.2, D4.2, J6.4, K2.4
PI_UART_RX: A1.1, J1.6
PI_UART_TX: A1.2, J1.5
RAIL_GATE: Q14.1, Q15.3, R106.2
RELAY_ENABLE_RAIL: D1.1, D3.1, D5.1, D7.1, D9.1, D11.1, D13.1, K1.1, K2.1, K3.1, K4.1, K5.1, K6.1, K7.1, Q14.3, TP16.1
RP2040_OK: A1.4, J1.13, R109.1, TP14.1
SAFE_STOP_RETURN: J8.4, Q14.2, R106.1, TP15.1
SAFE_TBSC_RETURN: J8.2, J8.3
SLOW_AUX1: R62.2, U2.26, U33.4
SLOW_AUX2: R64.2, U2.27, U34.4
SLOW_AUX3: R66.2, U2.28, U35.4
SLOW_BS: R44.2, U1.5, U24.4
SLOW_FOUL: R50.2, U1.8, U27.4
SLOW_GP: R40.2, U1.3, U22.4
SLOW_GS1: R20.2, U1.21, U12.4
SLOW_GS2: R22.2, U1.22, U13.4
SLOW_GS3: R24.2, U1.23, U14.4
SLOW_GS4: R26.2, U1.24, U15.4
SLOW_GS5: R28.2, U1.25, U16.4
SLOW_GS6: R30.2, U1.26, U17.4
SLOW_GS7: R32.2, U1.27, U18.4
SLOW_GS8: R34.2, U1.28, U19.4
SLOW_GS9: R36.2, U1.1, U20.4
SLOW_GS10: R38.2, U1.2, U21.4
SLOW_MAN_S: R56.2, U2.23, U30.4
SLOW_MAN_SWS: R58.2, U2.24, U31.4
SLOW_MAN_SWSR: R60.2, U2.25, U32.4
SLOW_MAN_T: R54.2, U2.22, U29.4
SLOW_OS: R42.2, U1.4, U23.4
SLOW_PBC: R48.2, U1.7, U26.4
SLOW_PBZ: R46.2, U1.6, U25.4
SLOW_TENTH: R52.2, U2.21, U28.4
SNUB_BE: C7.1, R78.2
SNUB_M: C8.1, R81.2
SNUB_M1: C10.1, R87.2
SNUB_M2: C9.1, R84.2
SNUB_S: C4.1, R69.2
SNUB_SP: C6.1, R75.2
SNUB_T: C5.1, R72.2
VCC_3V3: A1.36, C1.1, C2.1, C3.1, C14.1, J1.11, R1.1, R2.1, R4.1, R6.1, R8.1, R10.1, R12.1, R14.1, R16.1, R18.1, R20.1, R22.1, R24.1, R26.1, R28.1, R30.1, R32.1, R34.1, R36.1, R38.1, R40.1, R42.1, R44.1, R46.1, R48.1, R50.1, R52.1, R54.1, R56.1, R58.1, R60.1, R62.1, R64.1, R66.1, TP3.1, U1.9, U1.18, U2.9, U2.15, U2.18, U3.9, U3.16, U3.18
VCC_5V: A1.39, C12.1, D17.1, J1.1, J7.1, J8.1, R100.1, R101.1, TP1.1, U36.4, U36.8, U37.1
VCC_5V_RAW: D17.2, J2.1
WDOG_KICK: J1.7, R102.1, TP8.1
WDOG_KICK_DRAIN: D15.1, D16.1, Q12.3
WDOG_KICK_GATE: Q12.1, R102.2, R103.1
WDOG_OK_GATE: Q13.1, R104.2, R105.1
WDOG_OK_PULLDOWN: Q13.3, Q16.2, TP12.1
WDOG_TIMING_NODE: C11.1, D15.2, R100.2, TP9.1, U36.6, U36.7
